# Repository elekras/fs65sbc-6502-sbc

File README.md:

# fs65sbc
Simple single and small board (99.9 mm x 99.9 mm) computer with 6502/65C02

## Technical data:  
1x MICROPROCESSOR 65C02 @2MHz  
1x IDE 8 bit interface for CF card (read speed 86 kB/s)  
2x SPI interface for SD card  (read speed 5.6 kB/s)  
1x SERIAL PORT @38400 baud (38400-8-N-1) interrupt driven with handshake CTS/RTS  
1x SOFTWARE only tx serial port  
1x SYSTEM Timer 20 mS  
1x I2C port  
1x RTC with backup battery  
1x I2C eeprom AT24C256  
1x RESET button  
1x EXTERNAL reset pin  
1x DEBUG output pin  
1x SMALL interface connector  
1x BUZZER  
1x RESET supervisor  
1x VIA 65C02  
1x ACIA 65C51  
1x GAL address decoder  
128 KiB static ram with 8 KiB paged memory  
8 KiB (e)eprom  
7 KiB monitor m65  

### m65:    monitor m65 for fs65sbc  
### hw:     KICAD files  
### pld:    gal22v10 equations   
### img:    images and photos
### cpm-65: CPM-65 by Dietrich Lausberg https://github.com/dietrich-l for fs65sbc  
### bin:   PC utilities  

Connect the FS65SBC to PC using FT232RL modified USB-SERIAL adapters

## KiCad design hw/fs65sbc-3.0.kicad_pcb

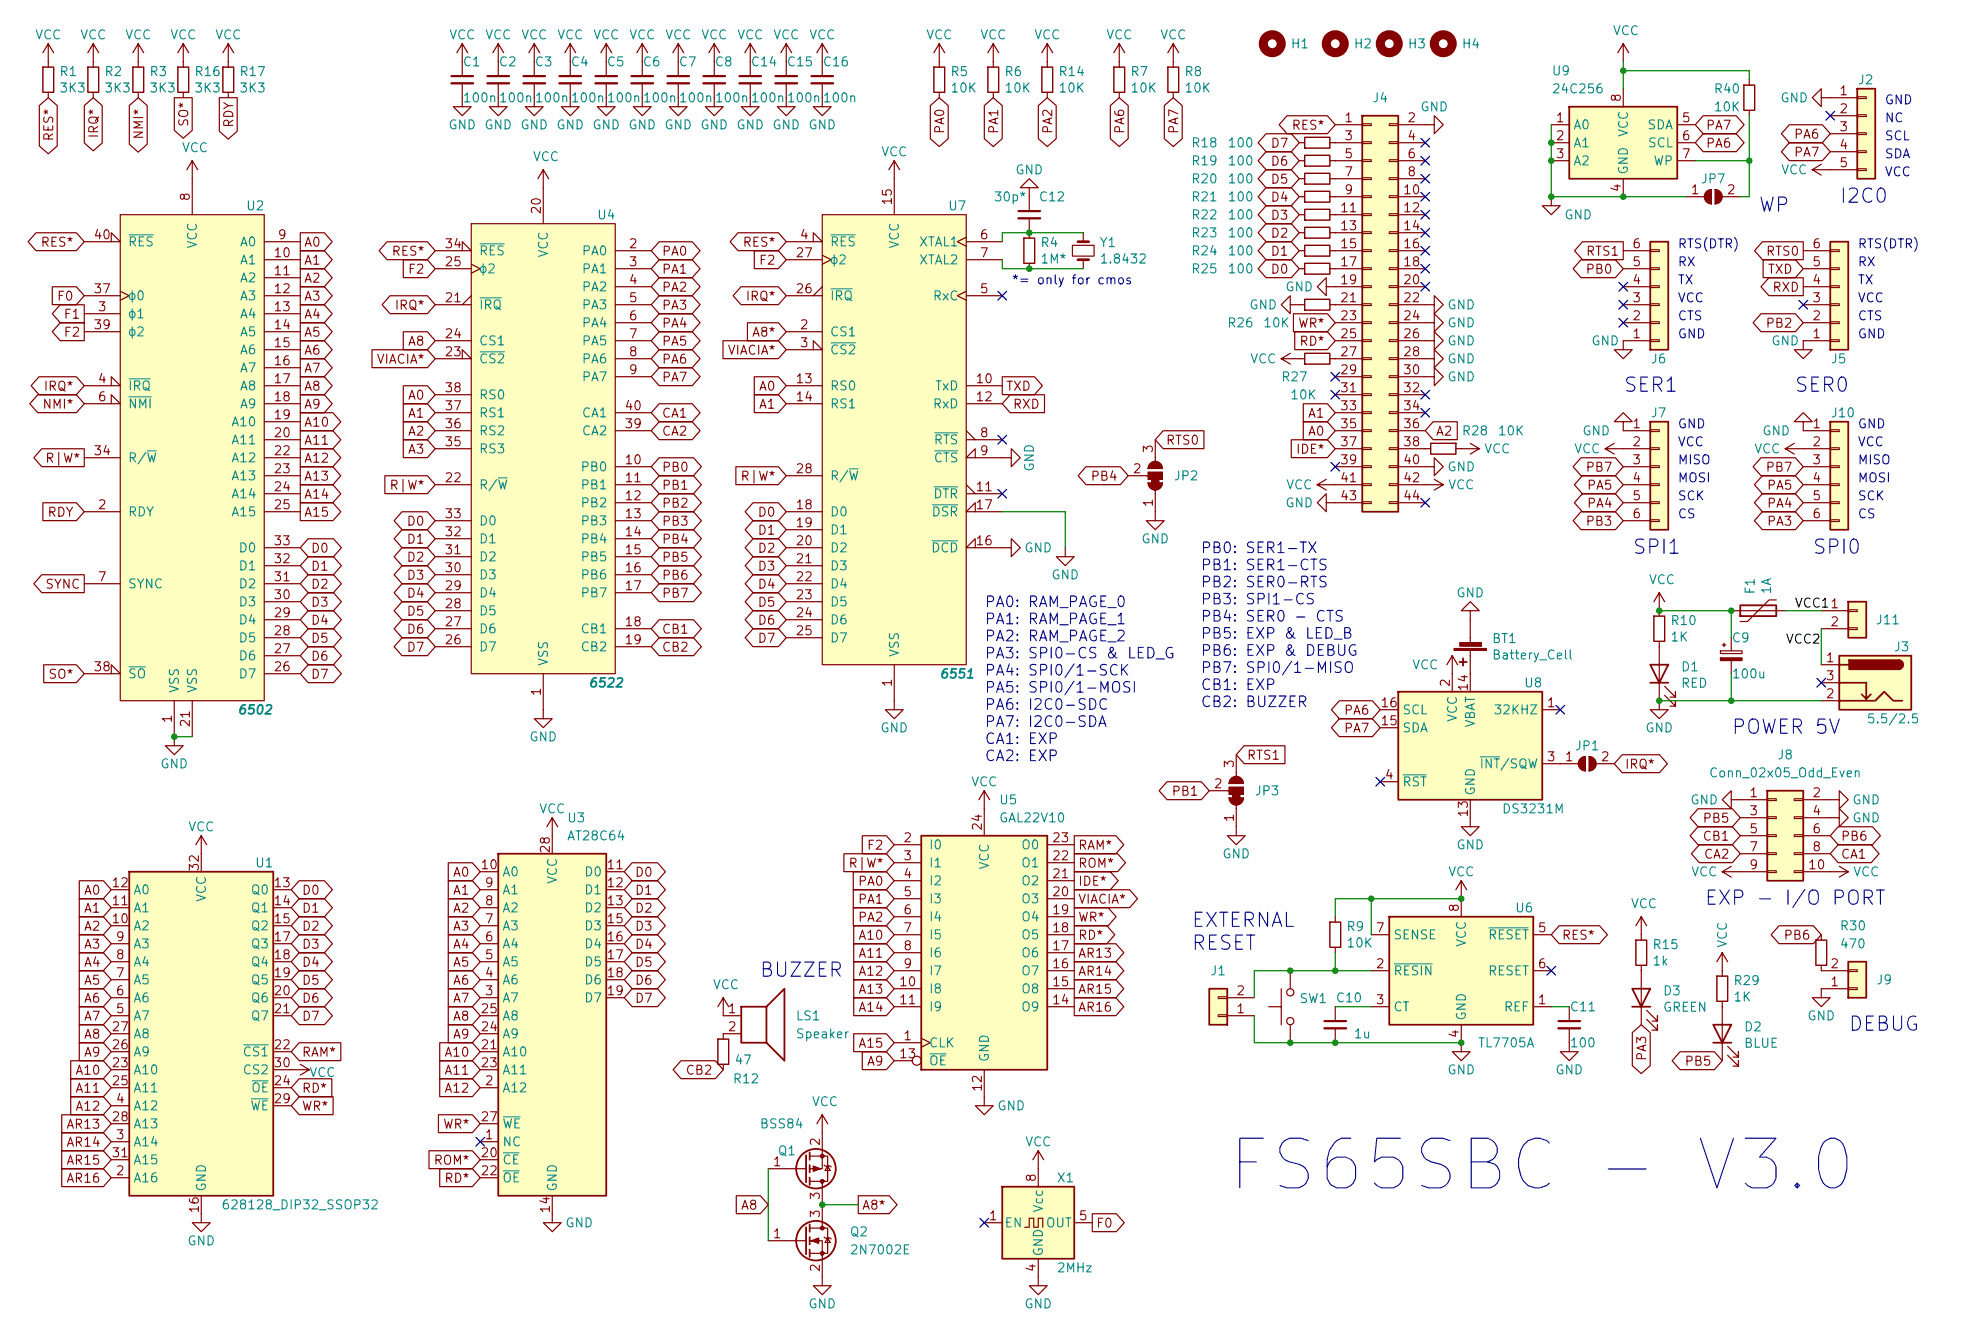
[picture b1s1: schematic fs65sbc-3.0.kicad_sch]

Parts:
BT1: Battery_Cell; BATTERY_HOLDER_CR2012
C1, C2, C3, C4, C5, C6, C7, C8, C14, C15, C16: 100n; C_0805_2012Metric_Pad1.18x1.45mm_HandSolder
C9: 100u; CP_Radial_D8.0mm_P3.50mm
C10: 1u; C_0805_2012Metric_Pad1.18x1.45mm_HandSolder
C11: 100; C_0805_2012Metric_Pad1.18x1.45mm_HandSolder
C12: 30p*; C_0805_2012Metric_Pad1.18x1.45mm_HandSolder
D1: RED; LED_0805_2012Metric_Pad1.15x1.40mm_HandSolder
D2: BLUE; LED_0805_2012Metric_Pad1.15x1.40mm_HandSolder
D3: GREEN; LED_0805_2012Metric_Pad1.15x1.40mm_HandSolder
F1: 1A; Fuse_1812_4532Metric_Castellated
H1, H2, H3, H4: MountingHole; MountingHole_3.2mm_M3_Pad
J1, J9, J11: Conn_01x02; PinSocket_1x02_P2.54mm_Vertical
J2: Conn_01x05; PinHeader_1x05_P2.54mm_Vertical
J3: 5.5/2.5; BarrelJack_Wuerth_6941xx301002
J4: Conn_02x22_Odd_Even; Edge_2x22_P2.00mm_SMD
J5, J6, J7, J10: Conn_01x05; PinHeader_1x06_P2.54mm_Vertical
J8: Conn_02x05_Odd_Even; PinHeader_2x05_P2.54mm_Vertical
JP1, JP7: SolderJumper_2_Open; SolderJumper-2_P1.3mm_Open_RoundedPad1.0x1.5mm
JP2, JP3: SolderJumper_3_Bridged12; SolderJumper-3_P1.3mm_Open_RoundedPad1.0x1.5mm
LS1: Speaker; Buzzer_12x9.5RM7.6
Q1: BSS84; SOT-23_Handsoldering
Q2: 2N7002E; SOT-23_Handsoldering
R1, R2, R3, R16, R17: 3K3; R_0805_2012Metric_Pad1.20x1.40mm_HandSolder
R4: 1M*; R_0805_2012Metric_Pad1.20x1.40mm_HandSolder
R5, R6, R7, R8, R9, R14, R26, R27, R28, R40: 10K; R_0805_2012Metric_Pad1.20x1.40mm_HandSolder
R10, R29: 1K; R_0805_2012Metric_Pad1.20x1.40mm_HandSolder
R12: 47; R_0805_2012Metric_Pad1.20x1.40mm_HandSolder
R15: 1k; R_0805_2012Metric_Pad1.20x1.40mm_HandSolder
R18, R19, R20, R21, R22, R23, R24, R25: 100; R_0805_2012Metric_Pad1.20x1.40mm_HandSolder
R30: 470; R_0805_2012Metric_Pad1.20x1.40mm_HandSolder
SW1: SW_Push; SW_PUSH_6mm_H4.3mm
U1: 628128_DIP32_SSOP32; DIP-32_W15.24mm_Socket
U2: 6502; DIP-40_W15.24mm_Socket
U3: AT28C64; DIP-28_W15.24mm
U4: 6522; DIP-40_W15.24mm_Socket
U5: GAL22V10; DIP-24_W7.62mm_Socket
U6: TL7705A; DIP-8_W7.62mm_Socket
U7: 6551; DIP-28_W15.24mm_Socket
U8: DS3231M; SOIC-16W_7.5x10.3mm_P1.27mm
U9: 24C256; DIP-8_W7.62mm_Socket
X1: 2MHz; Oscillator_DIP-8
Y1: 1.8432; Crystal_HC49-U_Vertical

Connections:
/VCC1: F1.2, J11.1
/VCC2: J3.1, J11.2
A0: J4.35, U1.12 (A0), U2.9 (A0), U3.10 (A0), U4.38 (RS0), U7.13 (RS0)
A1: J4.33, U1.11 (A1), U2.10 (A1), U3.9 (A1), U4.37 (RS1), U7.14 (RS1)
A2: J4.36, U1.10 (A2), U2.11 (A2), U3.8 (A2), U4.36 (RS2)
A3: U1.9 (A3), U2.12 (A3), U3.7 (A3), U4.35 (RS3)
A4: U1.8 (A4), U2.13 (A4), U3.6 (A4)
A5: U1.7 (A5), U2.14 (A5), U3.5 (A5)
A6: U1.6 (A6), U2.15 (A6), U3.4 (A6)
A7: U1.5 (A7), U2.16 (A7), U3.3 (A7)
A8: Q1.1 (G), Q2.1 (G), U1.27 (A8), U2.17 (A8), U3.25 (A8), U4.24 (CS1)
A8*: Q1.3 (D), Q2.3 (D), U7.2 (CS1)
A9: U1.26 (A9), U2.18 (A9), U3.24 (A9), U5.13 (~OE)
A10: U1.23 (A10), U2.19 (A10), U3.21 (A10), U5.7 (I5)
A11: U1.25 (A11), U2.20 (A11), U3.23 (A11), U5.8 (I6)
A12: U1.4 (A12), U2.22 (A12), U3.2 (A12), U5.9 (I7)
A13: U2.23 (A13), U5.10 (I8)
A14: U2.24 (A14), U5.11 (I9)
A15: U2.25 (A15), U5.1 (CLK)
AR13: U1.28 (A13), U5.17 (O6)
AR14: U1.3 (A14), U5.16 (O7)
AR15: U1.31 (A15), U5.15 (O8)
AR16: U1.2 (A16), U5.14 (O9)
CA1: J8.8, U4.40 (CA1)
CA2: J8.7, U4.39 (CA2)
CB1: J8.5, U4.18 (CB1)
CB2: R12.2, U4.19 (CB2)
D0: R25.1, U1.13 (Q0), U2.33 (D0), U3.11 (D0), U4.33 (D0), U7.18 (D0)
D1: R24.1, U1.14 (Q1), U2.32 (D1), U3.12 (D1), U4.32 (D1), U7.19 (D1)
D2: R23.1, U1.15 (Q2), U2.31 (D2), U3.13 (D2), U4.31 (D2), U7.20 (D2)
D3: R22.1, U1.17 (Q3), U2.30 (D3), U3.15 (D3), U4.30 (D3), U7.21 (D3)
D4: R21.1, U1.18 (Q4), U2.29 (D4), U3.16 (D4), U4.29 (D4), U7.22 (D4)
D5: R20.1, U1.19 (Q5), U2.28 (D5), U3.17 (D5), U4.28 (D5), U7.23 (D5)
D6: R19.1, U1.20 (Q6), U2.27 (D6), U3.18 (D6), U4.27 (D6), U7.24 (D6)
D7: R18.1, U1.21 (Q7), U2.26 (D7), U3.19 (D7), U4.26 (D7), U7.25 (D7)
F0: U2.37 (ϕ0), X1.5 (OUT)
F1: U2.3 (ϕ1)
F2: U2.39 (ϕ2), U4.25 (ϕ2), U5.2 (I0), U7.27 (ϕ2)
GND: BT1.2 (-), C1.2, C2.2, C3.2, C4.2, C5.2, C6.2, C7.2, C8.2, C9.2, C10.2, C11.2, C12.1, C14.2, C15.2, C16.2, D1.1 (K), J1.1, J2.1, J3.2, J4.2, J4.19, J4.22, J4.24, J4.26, J4.28, J4.30, J4.40, J4.43, J5.1, J6.1, J7.1, J8.1, J8.2, J8.4, J9.1, J10.1, JP2.1 (A), JP3.1 (A), JP7.1 (A), Q2.2 (S), R26.1, SW1.1, U1.16 (GND), U2.1 (VSS), U2.21 (VSS), U3.14 (GND), U4.1 (VSS), U5.12 (GND), U6.4 (GND), U7.1 (VSS), U7.9 (~CTS), U7.16 (~DCD), U7.17 (~DSR), U8.5 (GND), U8.6 (GND), U8.7 (GND), U8.8 (GND), U8.9 (GND), U8.10 (GND), U8.11 (GND), U8.12 (GND), U8.13 (GND), U9.1 (A0), U9.2 (A1), U9.3 (A2), U9.4 (GND), X1.4 (GND)
IDE*: J4.37, U5.21 (O2)
IRQ*: JP1.2 (B), R2.2, U2.4 (~IRQ), U4.21 (~IRQ), U7.26 (~IRQ)
NMI*: R3.2, U2.6 (~NMI)
unnamed: BT1.1 (+), U8.14 (VBAT)
unnamed: C10.1, U6.3 (CT)
unnamed: C11.1, U6.1 (REF)
unnamed: C12.2, R4.1, U7.6 (XTAL1), Y1.1
unnamed: D1.2 (A), R10.2
unnamed: D2.2 (A), R29.2
unnamed: D3.2 (A), R15.2
unnamed: J1.2, R9.2, SW1.2, U6.2 (~RESIN)
unnamed: J4.3, R18.2
unnamed: J4.5, R19.2
unnamed: J4.7, R20.2
unnamed: J4.9, R21.2
unnamed: J4.11, R22.2
unnamed: J4.13, R23.2
unnamed: J4.15, R24.2
unnamed: J4.17, R25.2
unnamed: J4.21, R26.2
unnamed: J4.27, R27.2
unnamed: J4.38, R28.2
unnamed: J9.2, R30.2
unnamed: JP1.1 (A), U8.3 (~INT/SQW)
unnamed: JP7.2 (B), R40.2, U9.7 (WP)
unnamed: LS1.2, R12.1
unnamed: R4.2, U7.7 (XTAL2), Y1.2
PA0: R5.2, U4.2 (PA0), U5.4 (I2)
PA1: R6.2, U4.3 (PA1), U5.5 (I3)
PA2: R14.2, U4.4 (PA2), U5.6 (I4)
PA3: D3.1 (K), J10.6, U4.5 (PA3)
PA4: J7.5, J10.5, U4.6 (PA4)
PA5: J7.4, J10.4, U4.7 (PA5)
PA6: J2.3, R7.2, U4.8 (PA6), U8.16 (SCL), U9.6 (SCL)
PA7: J2.4, R8.2, U4.9 (PA7), U8.15 (SDA), U9.5 (SDA)
PB0: J6.5, U4.10 (PB0)
PB1: JP3.2 (C), U4.11 (PB1)
PB2: J5.2, U4.12 (PB2)
PB3: J7.6, U4.13 (PB3)
PB4: JP2.2 (C), U4.14 (PB4)
PB5: D2.1 (K), J8.3, U4.15 (PB5)
PB6: J8.6, R30.1, U4.16 (PB6)
PB7: J7.3, J10.3, U4.17 (PB7)
RAM*: U1.22 (~CS1), U5.23 (O0)
RD*: J4.25, U1.24 (~OE), U3.22 (~OE), U5.18 (O5)
RDY: R17.2, U2.2 (RDY)
RES*: J4.1, R1.2, U2.40 (~RES), U4.34 (~RES), U6.5 (~RESET), U7.4 (~RES)
ROM*: U3.20 (~CE), U5.22 (O1)
RTS0: J5.6, JP2.3 (B)
RTS1: J6.6, JP3.3 (B)
RXD: J5.4, U7.12 (RxD)
R|W*: U2.34 (R/~W), U4.22 (R/~W), U5.3 (I1), U7.28 (R/~W)
SO*: R16.2, U2.38 (~SO)
SYNC: U2.7 (SYNC)
TXD: J5.5, U7.10 (TxD)
VCC: C1.1, C2.1, C3.1, C4.1, C5.1, C6.1, C7.1, C8.1, C9.1, C14.1, C15.1, C16.1, F1.1, J2.5, J4.41, J4.42, J7.2, J8.9, J8.10, J10.2, LS1.1, Q1.2 (S), R1.1, R2.1, R3.1, R5.1, R6.1, R7.1, R8.1, R9.1, R10.1, R14.1, R15.1, R16.1, R17.1, R27.1, R28.1, R29.1, R40.1, U1.30 (CS2), U1.32 (VCC), U2.8 (VCC), U3.28 (VCC), U4.20 (VCC), U5.24 (VCC), U6.7 (SENSE), U6.8 (VCC), U7.15 (VCC), U8.2 (VCC), U9.8 (VCC), X1.8 (Vcc)
VIACIA*: U4.23 (~CS2), U5.20 (O3), U7.3 (~CS2)
WR*: J4.23, U1.29 (~WE), U3.27 (~WE), U5.19 (O4)

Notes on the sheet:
PA0: RAM_PAGE_0 PA1: RAM_PAGE_1 PA2: RAM_PAGE_2 PA3: SPI0-CS & LED_G PA4: SPI0/1-SCK PA5: SPI0/1-MOSI PA6: I2C0-SDC PA7: I2C0-SDA CA1: EXP CA2: EXP
MOSI
DEBUG
VCC
RTS(DTR)
GND
*= only for cmos
SER1
SCK
FS65SBC - V3.0
BUZZER
EXP - I/O PORT
SPI1
CTS
PB0: SER1-TX PB1: SER1-CTS PB2: SER0-RTS PB3: SPI1-CS PB4: SER0 - CTS PB5: EXP & LED_B PB6: EXP & DEBUG PB7: SPI0/1-MISO CB1: EXP CB2: BUZZER
MISO
SER0
SDA
EXTERNAL RESET
I2C0
SCL
SPI0
POWER 5V

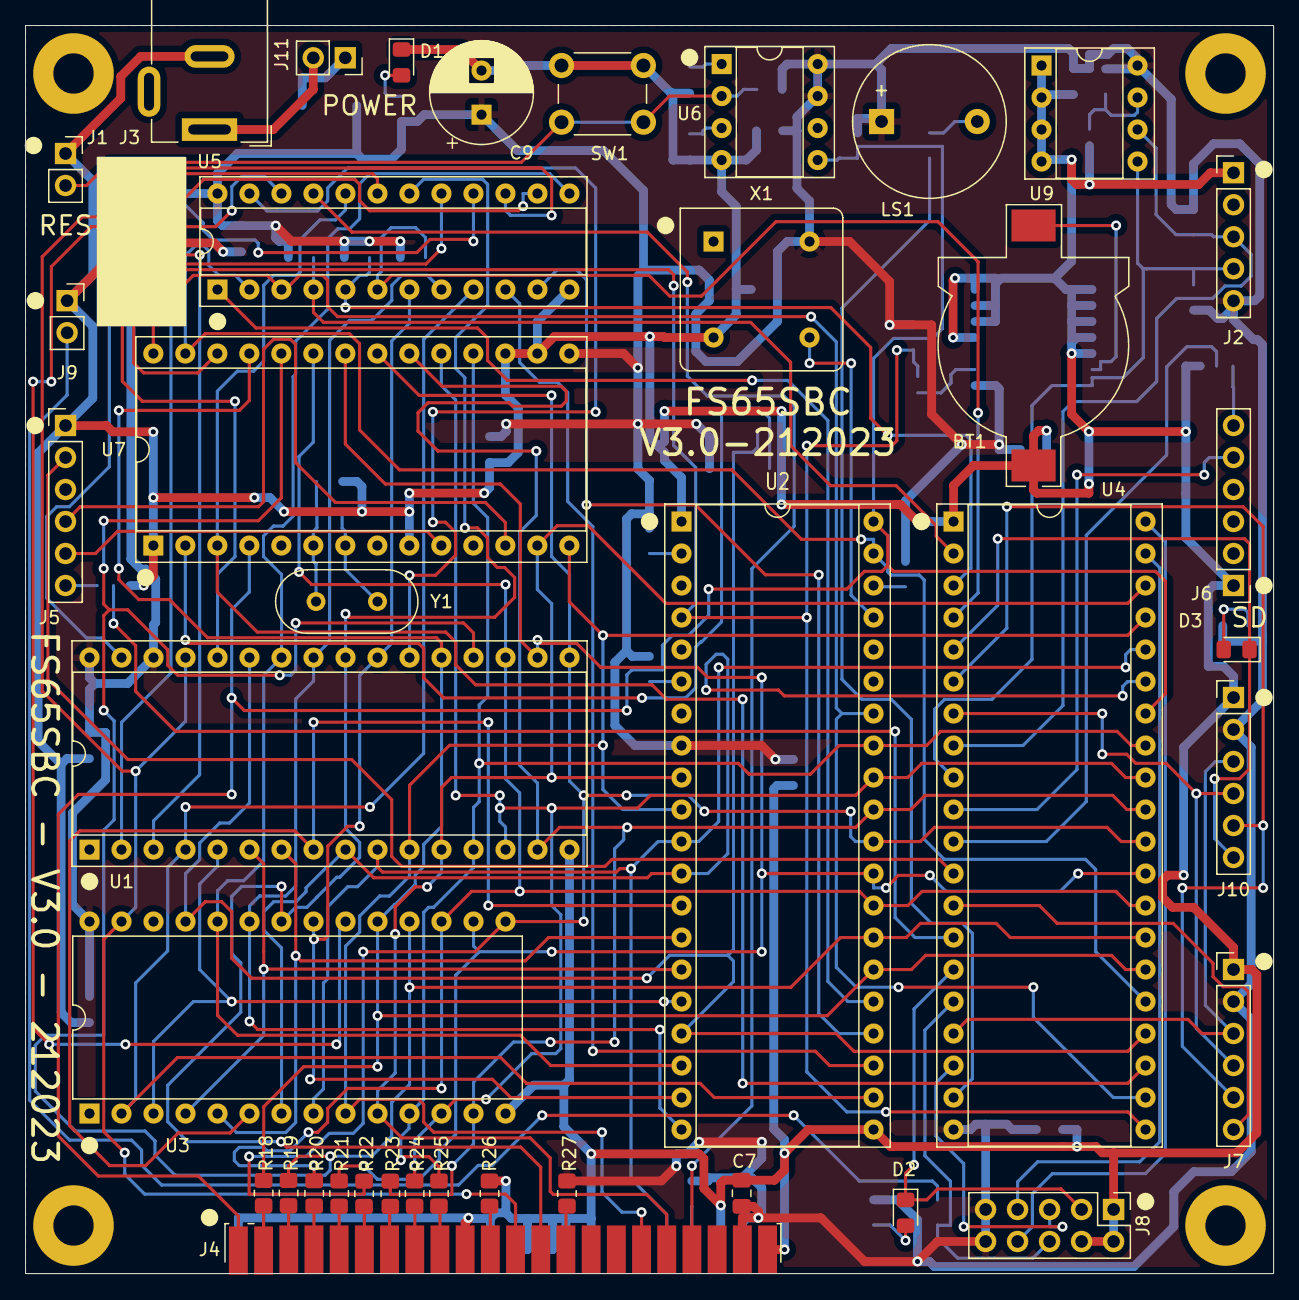
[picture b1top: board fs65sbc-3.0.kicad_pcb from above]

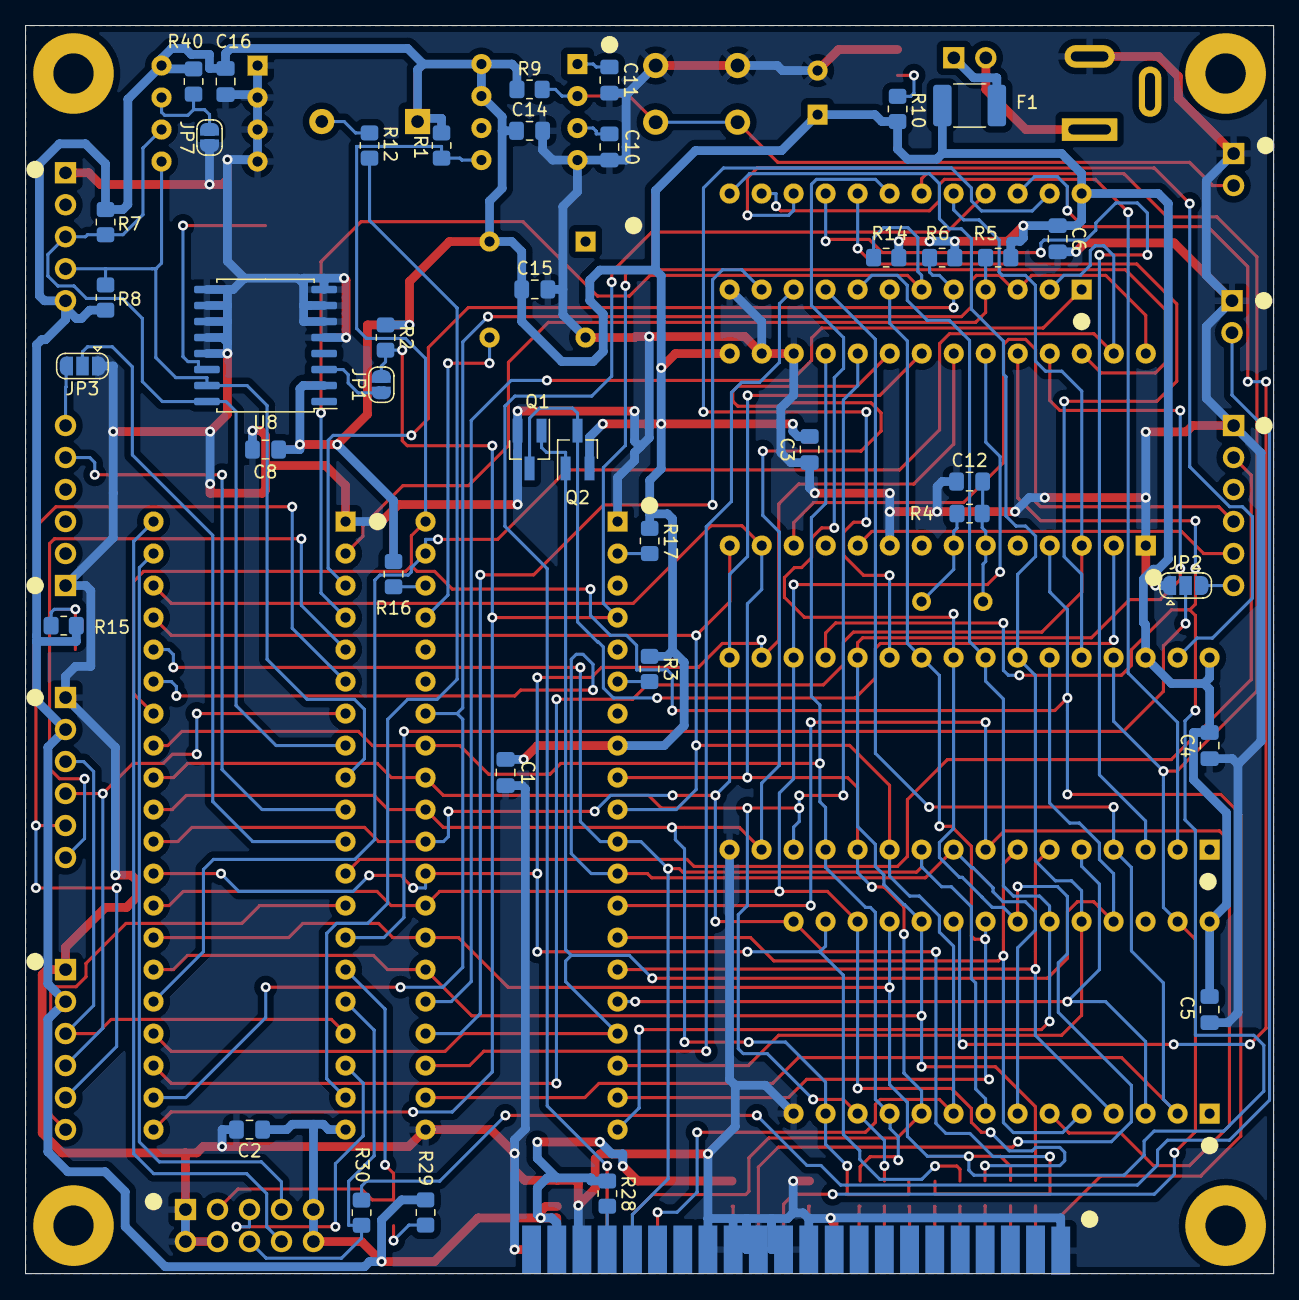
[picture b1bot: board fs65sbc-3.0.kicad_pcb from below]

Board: 2 copper layers, 99.1 x 99.1 mm, 83 parts (40 on the bottom side), 95 nets.

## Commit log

2025-03-25 Add files via upload
    FS65SBC is a simple single board computer for 6502/65C02.
    1x interrupt driven serial interface @ 38400 baud with CTS/RTS handshaking
    1x low speed aux software serial port only for tx
    2x SPI interface for SD CARD
    1xIDE interface for CF CARD
    1xI2C interface
